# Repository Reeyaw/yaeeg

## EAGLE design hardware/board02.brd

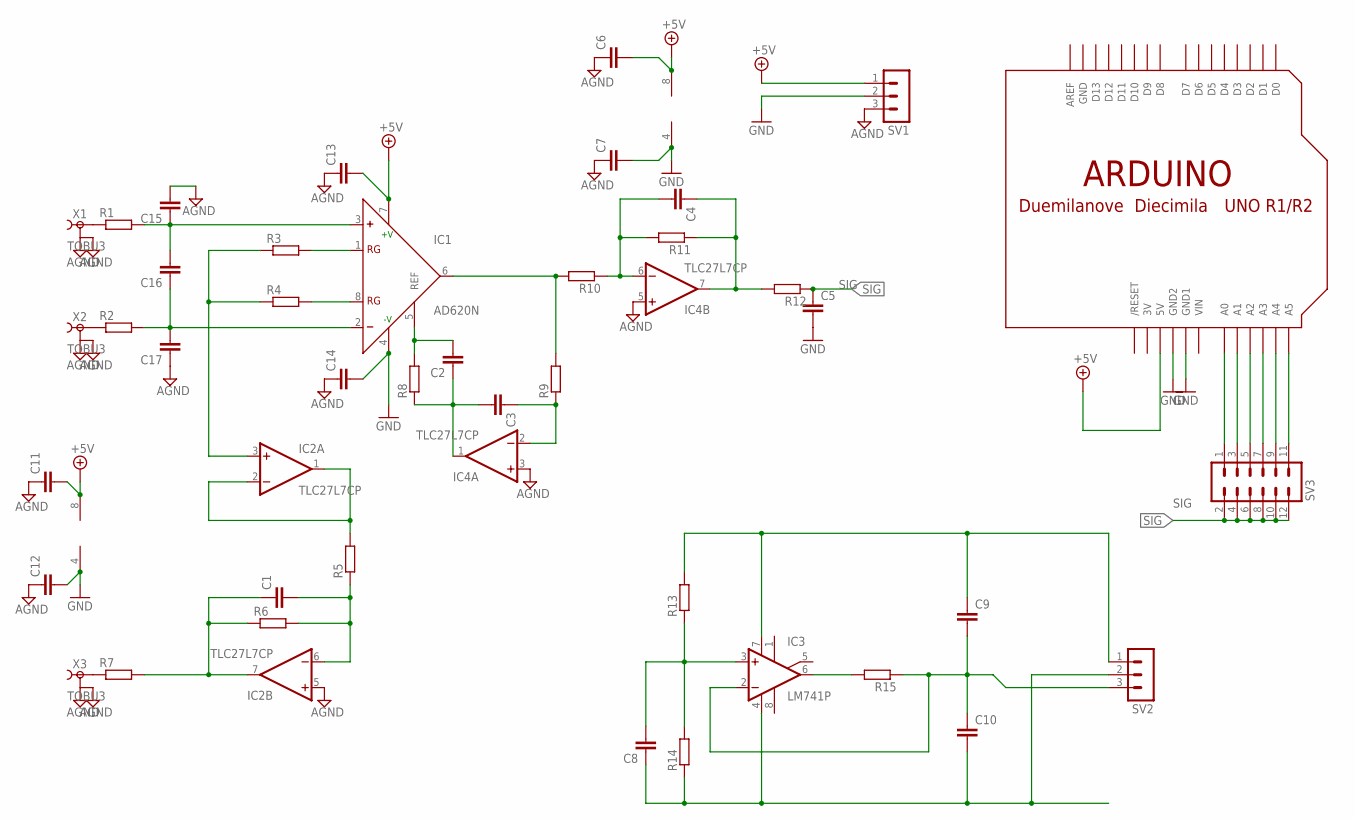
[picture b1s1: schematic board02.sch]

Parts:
C1, C2, C3, C4: C-EU050-050X075; C050-050X075
C5, C6, C7, C8, C9, C10, C11, C12, C13, C14, C15, C16, C17: C-EU050-025X075; C050-025X075
IC1: AD620N; DIL08
IC2, IC4: TLC27L7CP; DIL08
IC3: LM741P; DIL08
R1, R2, R3, R4, R5, R6, R7, R8, R9, R10, R11, R12, R13, R14, R15: R-EU_0204/7; 0204/7
SV1, SV2: MA03-1
SV3: MA06-2
U$2: ARDUINO-NC; ARDUINO-NOCONN
X1, X2, X3: TOBU3

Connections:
3V: U$2.3V
+5V: C6.2, C11.2, C13.2, IC1.7 (+V), IC2.8 (VDD), IC4.8 (VDD), SV1.1, U$2.5V
AGND: C6.1, C7.1, C11.1, C12.1, C13.1, C14.1, C15.2, C17.1, IC2.5 (+IN), IC4.3 (+IN), IC4.5 (+IN), SV1.3, X1.2, X1.2@1 (2), X1.2@2 (2), X2.2, X2.2@1 (2), X2.2@2 (2), X3.2, X3.2@1 (2), X3.2@2 (2)
GND: C5.2, C7.2, C12.2, C14.2, IC1.4 (-V), IC2.4 (GND), IC4.4 (GND), SV1.2, U$2.GND, U$2.GND1, U$2.GND2
unnamed: C15.1, C16.2, IC1.3 (+), R1.2
unnamed: C16.1, C17.2, IC1.2 (-), R2.2
unnamed: IC1.1 (RG), R3.2
unnamed: IC1.8 (RG), R4.2
unnamed: C1.1, IC2.7 (OUT), R6.1, R7.2
unnamed: IC2.3 (+IN), R3.1, R4.1
unnamed: IC2.1 (OUT), IC2.2 (-IN), R5.2
unnamed: C1.2, IC2.6 (-IN), R5.1, R6.2
unnamed: C2.1, C3.2, IC4.1 (OUT), R8.1
unnamed: C2.2, IC1.5 (REF), R8.2
unnamed: IC1.6 (OUT), R9.2, R10.2
unnamed: C3.1, IC4.2 (-IN), R9.1
unnamed: C4.2, IC4.6 (-IN), R10.1, R11.2
unnamed: C4.1, IC4.7 (OUT), R11.1, R12.2
unnamed: R1.1, X1.1
unnamed: R2.1, X2.1
unnamed: R7.1, X3.1
unnamed: C8.1, C10.2, IC3.4 (V-), R14.1, SV2.2
unnamed: C8.2, IC3.3 (+IN), R13.1, R14.2
unnamed: C9.1, IC3.7 (V+), R13.2, SV2.1
unnamed: IC3.6 (OUT), R15.2
unnamed: C9.2, C10.1, IC3.2 (-IN), R15.1, SV2.3
unnamed: SV3.1, U$2.A0
unnamed: SV3.3, U$2.A1
unnamed: SV3.5, U$2.A2
unnamed: SV3.7, U$2.A3
unnamed: SV3.9, U$2.A4
unnamed: SV3.11, U$2.A5
SIG: C5.1, R12.1, SV3.2, SV3.4, SV3.6, SV3.8, SV3.10, SV3.12
VIN: U$2.VIN

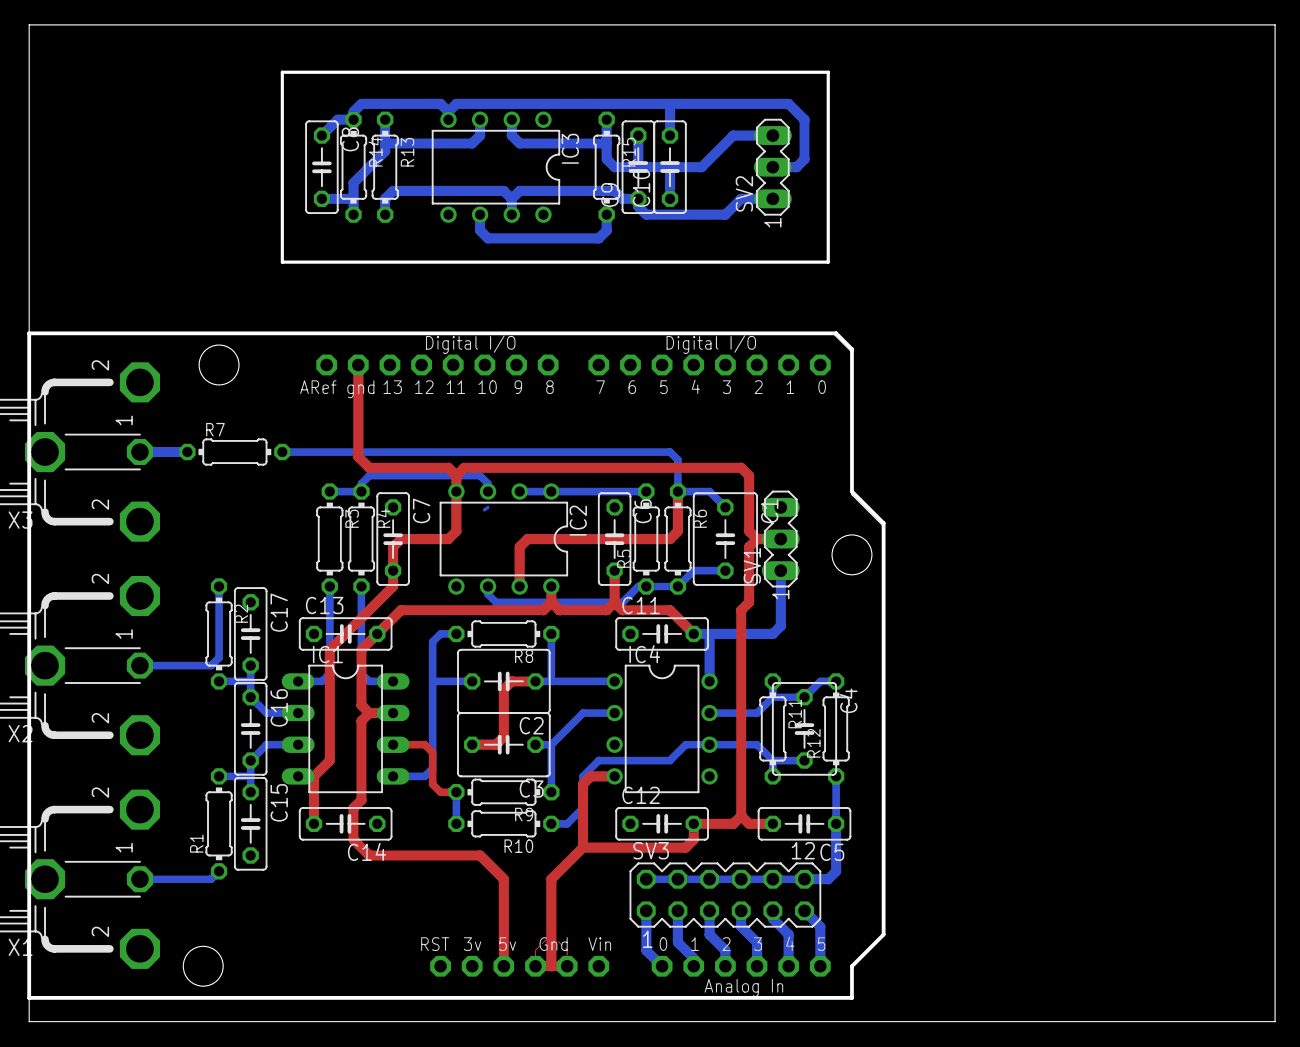
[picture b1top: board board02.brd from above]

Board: 2 copper layers, 99.8 x 79.7 mm, 43 parts (0 on the bottom side), 32 nets.

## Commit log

2013-12-09 Initial version (board 02)
2016-01-30 Migrating wiki contents from Google Code
